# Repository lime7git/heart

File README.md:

# heart
A small gift. Heart shape PCB with STM32L0 microcontroller, TCA6416A I2C GPIO expander, LIS3DH accelerometer, BS812A touch sensor and some fancy leds.
 
It can be used as a keychain. It is operates on a CR2450 coin cell battery. There is a few led patterns which can be start by press a touch button or shake. When the device does not recognize any event in 10 seconds it will enter the low power mode and can be woke up only by touching button. In this mode the power consumption is about 25 uA. 

YouTube video short presentation :

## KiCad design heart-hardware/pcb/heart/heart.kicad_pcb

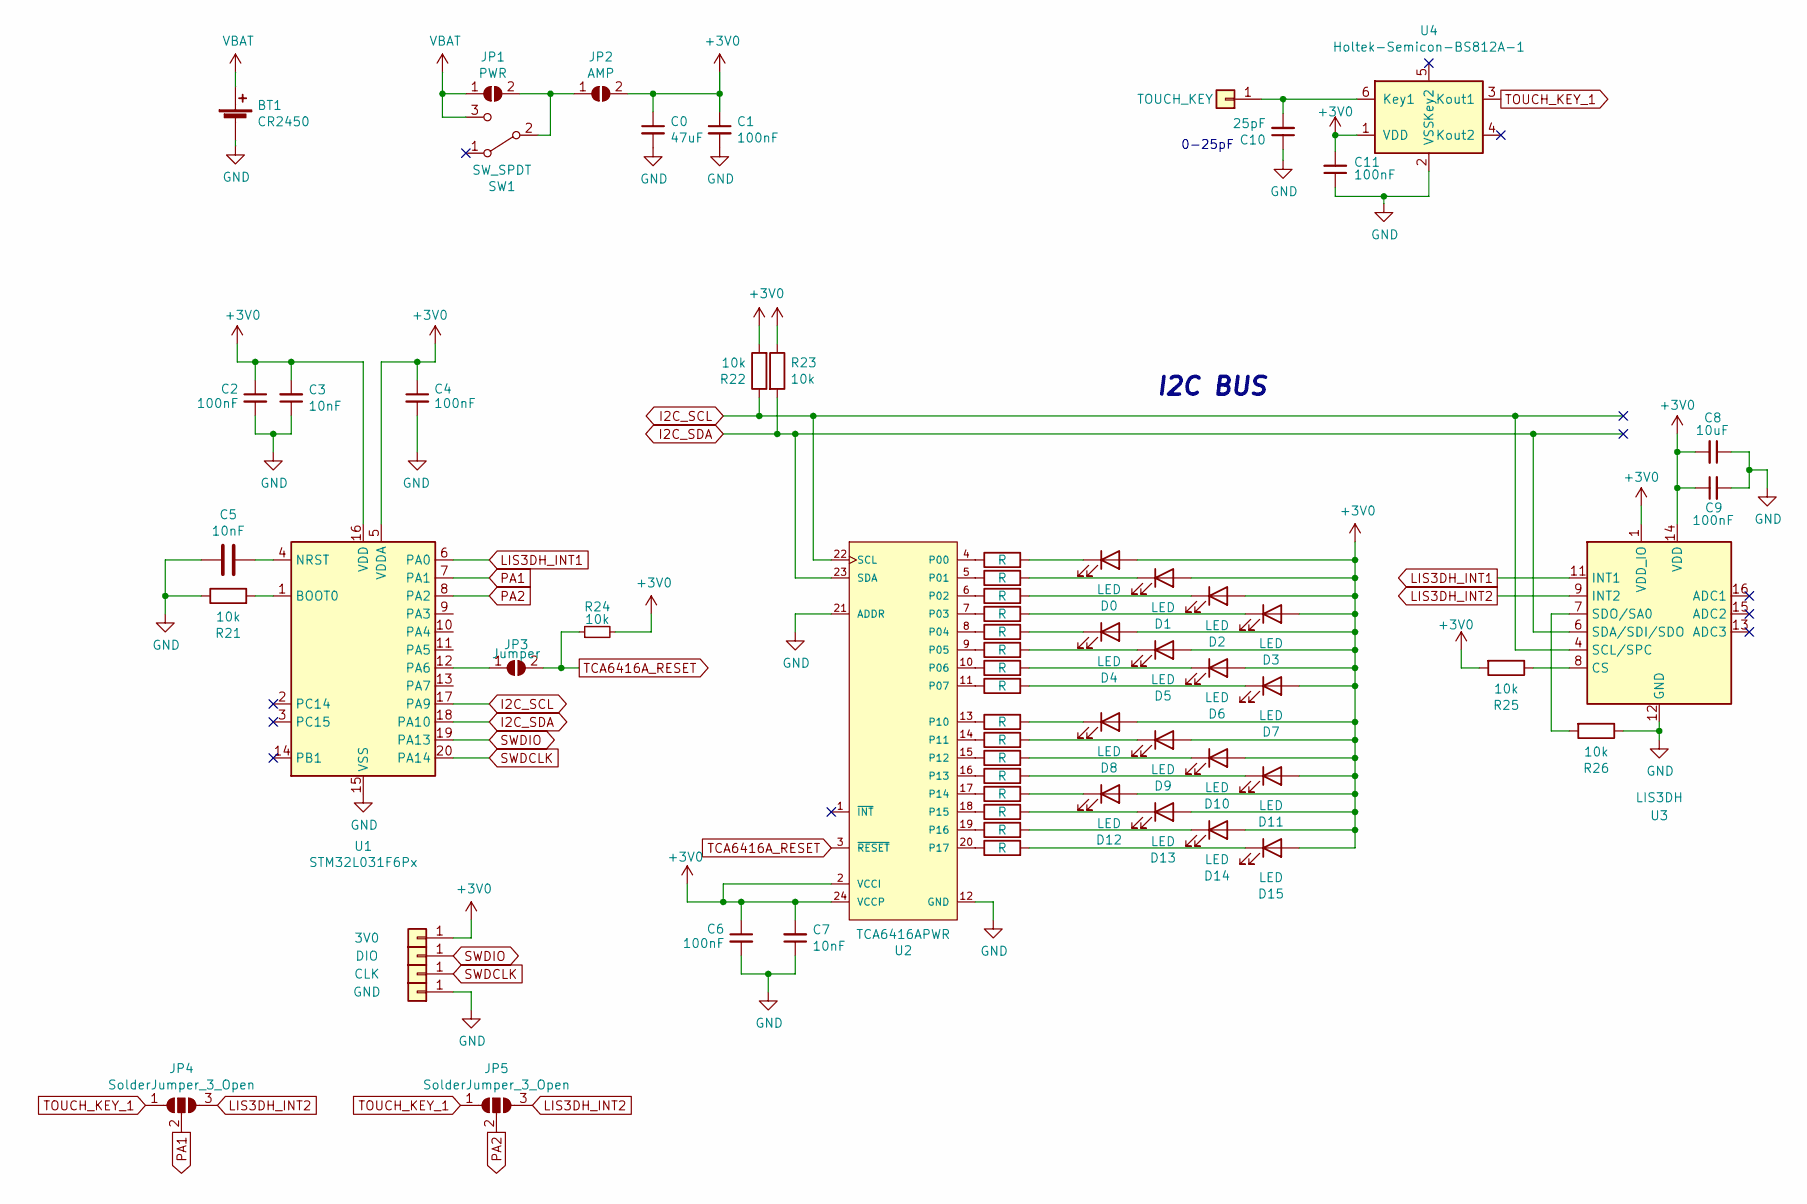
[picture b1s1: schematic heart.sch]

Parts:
BT1: CR2450; BatteryHolder_Keystone_3008_1x2450; LCSC C238100
C0: 47uF; C_1210_3225Metric_Pad1.33x2.70mm_HandSolder; LCSC C2918508
C1: 100nF; C_0402_1005Metric
C2, C4, C6, C9, C11: 100nF; C_0402_1005Metric; LCSC C60474
C3, C5, C7: 10nF; C_0402_1005Metric; LCSC C60133
C8: 10uF; C_0402_1005Metric; LCSC C15525
C10: 25pF; C_0402_1005Metric; LCSC C295971
D0, D1, D2, D3, D4, D5, D6, D7, D8, D9, D10, D11, D12, D13, D14, D15: LED; LED_0603_1608Metric; LCSC C2846646
J1: 3V0; TestPoint_Pad_1.0x1.0mm
J2: DIO; TestPoint_Pad_1.0x1.0mm
J3: CLK; TestPoint_Pad_1.0x1.0mm
J4: GND; TestPoint_Pad_1.0x1.0mm
J5: TOUCH_KEY; TestPoint_Pad_D4.0mm
JP1: PWR; SolderJumper-2_P1.3mm_Open_RoundedPad1.0x1.5mm
JP2: AMP; SolderJumper-2_P1.3mm_Open_RoundedPad1.0x1.5mm
JP3: Jumper; SolderJumper-2_P1.3mm_Open_RoundedPad1.0x1.5mm
JP4, JP5: SolderJumper_3_Open; SolderJumper-3_P1.3mm_Open_RoundedPad1.0x1.5mm_NumberLabels
R0, R1, R2, R3, R4, R5, R6, R7, R8, R9, R10, R11, R12, R13, R14, R15: R; R_0402_1005Metric; LCSC C258126
R21, R22, R23, R24, R25, R26: 10k; R_0402_1005Metric; LCSC C258091
SW1: SW_SPDT; SW_SPDT_PCM12; LCSC C221841
U1: STM32L031F6Px; TSSOP-20_4.4x6.5mm_P0.65mm; LCSC C115208
U2: TCA6416APWR; TSSOP-24_4.4x7.8mm_P0.65mm; 5V Tolerant IO Yes; LCSC C130203
U3: LIS3DH; LGA-16_3x3mm_P0.5mm_LayoutBorder3x5y; LCSC C15134
U4: Holtek-Semicon-BS812A-1; SOT-23-6; LCSC C81747

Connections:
+3V0: C0.1, C1.1, C2.1, C3.2, C4.1, C6.1, C7.2, C8.2, C9.1, C11.2, D0.2 (A), D1.2 (A), D2.2 (A), D3.2 (A), D4.2 (A), D5.2 (A), D6.2 (A), D7.2 (A), D8.2 (A), D9.2 (A), D10.2 (A), D11.2 (A), D12.2 (A), D13.2 (A), D14.2 (A), D15.2 (A), J1.1, JP2.2 (B), R22.2, R23.1, R24.2, R25.2, U1.5 (VDDA), U1.16 (VDD), U2.2 (VCCI), U2.24 (VCCP), U3.1 (VDD_IO), U3.14 (VDD), U4.1 (VDD)
GND: BT1.2 (-), C0.2, C1.2, C2.2, C3.1, C4.2, C5.2, C6.2, C7.1, C8.1, C9.2, C10.1, C11.1, J4.1, R21.1, R26.1, U1.15 (VSS), U2.12 (GND), U2.21 (ADDR), U3.5 (GND), U3.10 (GND), U3.12 (GND), U4.2 (VSS); also elsewhere on the board
I2C_SCL: R22.1, U1.17 (PA9), U2.22 (SCL), U3.4 (SCL/SPC)
I2C_SDA: R23.2, U1.18 (PA10), U2.23 (SDA), U3.6 (SDA/SDI/SDO)
LIS3DH_INT1: U1.6 (PA0), U3.11 (INT1)
LIS3DH_INT2: JP4.3 (B), JP5.3 (B), U3.9 (INT2); also elsewhere on the board
unnamed: C5.1, U1.4 (NRST)
unnamed: C10.2, J5.1, U4.6 (Key1)
unnamed: D0.1 (K), R0.2
unnamed: D1.1 (K), R1.2
unnamed: D2.1 (K), R2.2
unnamed: D3.1 (K), R3.2
unnamed: D4.1 (K), R4.2
unnamed: D5.1 (K), R5.2
unnamed: D6.1 (K), R6.2
unnamed: D7.1 (K), R7.2
unnamed: D8.1 (K), R8.2
unnamed: D9.1 (K), R9.2
unnamed: D10.1 (K), R10.2
unnamed: D11.1 (K), R11.2
unnamed: D12.1 (K), R12.2
unnamed: D13.1 (K), R13.2
unnamed: D14.1 (K), R14.2
unnamed: D15.1 (K), R15.2
unnamed: JP1.2 (B), JP2.1 (A), SW1.2 (B)
unnamed 25: JP3.1 (A), U1.12 (PA6); also elsewhere on the board
unnamed: R0.1, U2.4 (P00)
unnamed: R1.1, U2.5 (P01)
unnamed: R2.1, U2.6 (P02)
unnamed: R3.1, U2.7 (P03)
unnamed: R4.1, U2.8 (P04)
unnamed: R5.1, U2.9 (P05)
unnamed: R6.1, U2.10 (P06)
unnamed: R7.1, U2.11 (P07)
unnamed: R8.1, U2.13 (P10)
unnamed: R9.1, U2.14 (P11)
unnamed: R10.1, U2.15 (P12)
unnamed: R11.1, U2.16 (P13)
unnamed: R12.1, U2.17 (P14)
unnamed: R13.1, U2.18 (P15)
unnamed: R14.1, U2.19 (P16)
unnamed: R15.1, U2.20 (P17)
unnamed: R21.2, U1.1 (BOOT0)
unnamed: R25.1, U3.8 (CS)
unnamed: R26.2, U3.7 (SDO/SA0)
PA1: JP4.2 (C), U1.7 (PA1); also elsewhere on the board
PA2: JP5.2 (C), U1.8 (PA2); also elsewhere on the board
SWDCLK: J3.1, U1.20 (PA14)
SWDIO: J2.1, U1.19 (PA13)
TCA6416A_RESET: JP3.2 (B), R24.1, U2.3 (~RESET~); also elsewhere on the board
TOUCH_KEY_1: JP4.1 (A), JP5.1 (A), U4.3 (Kout1); also elsewhere on the board
VCC: BT1.1 (+), JP1.1 (A), SW1.3 (C); also elsewhere on the board

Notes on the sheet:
I2C BUS
0-25pF

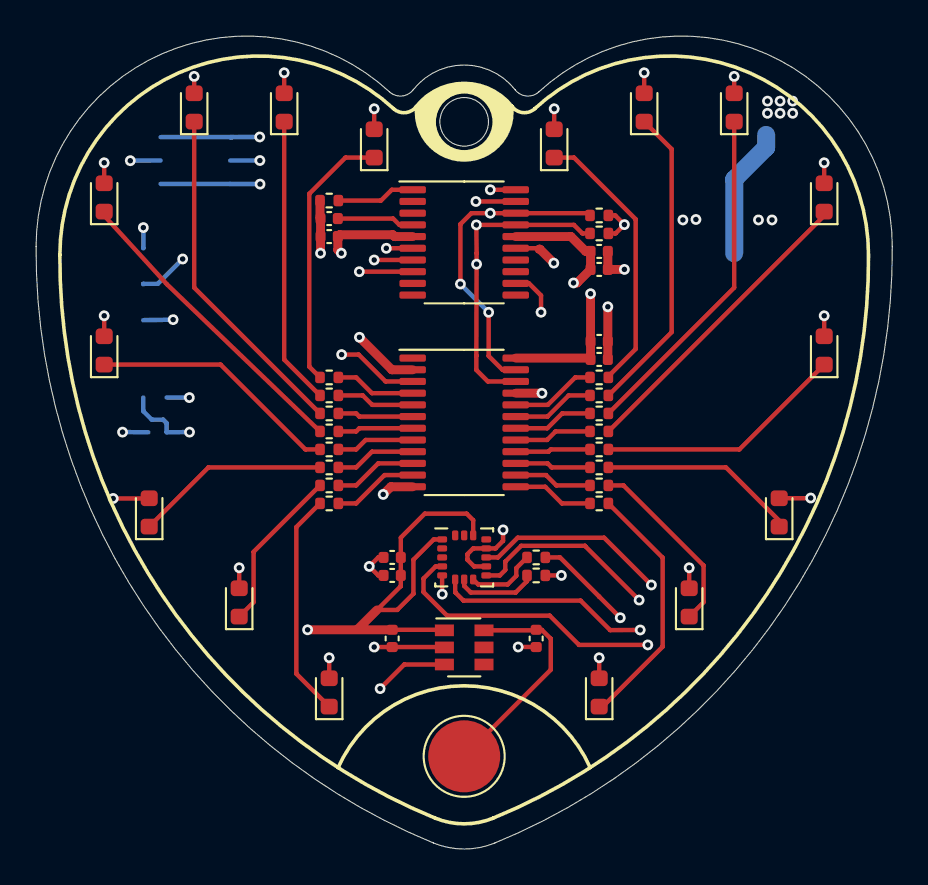
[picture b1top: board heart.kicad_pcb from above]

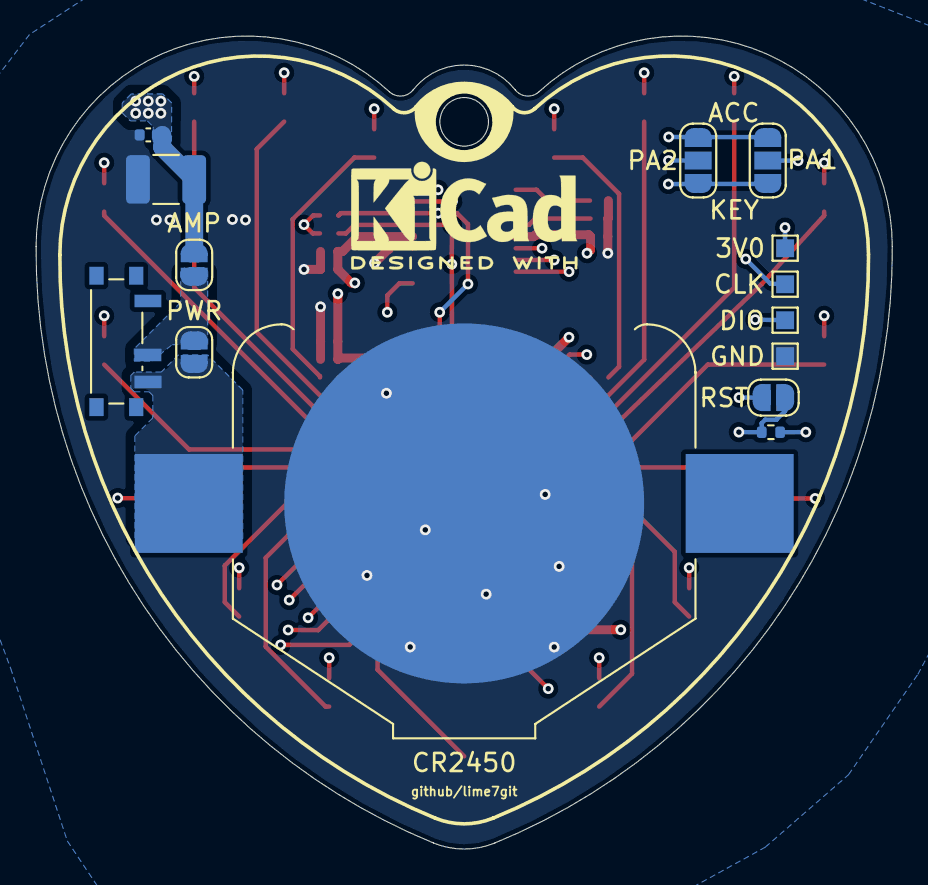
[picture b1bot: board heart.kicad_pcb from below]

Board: 4 copper layers, 47.6 x 45.2 mm, 66 parts (14 on the bottom side), 52 nets.

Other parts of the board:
CR2450: CR2450; BatteryHolder_Keystone_3008_1x2450
PA1, PA2: SolderJumper_3_Open; SolderJumper-3_P1.3mm_Open_RoundedPad1.0x1.5mm_NumberLabels
RST: Jumper; SolderJumper-2_P1.3mm_Open_RoundedPad1.0x1.5mm

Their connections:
GND: CR2450.2; also elsewhere on the board
LIS3DH_INT2: PA1.3, PA2.3; also elsewhere on the board
unnamed 25: RST.1; also elsewhere on the board
PA1: PA1.2; also elsewhere on the board
PA2: PA2.2; also elsewhere on the board
TCA6416A_RESET: RST.2; also elsewhere on the board
TOUCH_KEY_1: PA1.1, PA2.1; also elsewhere on the board
VCC: CR2450.1; also elsewhere on the board

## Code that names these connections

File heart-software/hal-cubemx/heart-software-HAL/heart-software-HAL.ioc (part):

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Mcu.Name=STM32L031F(4-6)Px
Mcu.Package=TSSOP20
Mcu.UserName=STM32L031F6Px
PA0-CK_IN.GPIOParameters=GPIO_Label
PA0-CK_IN.GPIO_Label=LIS3DH_INT1
PA0-CK_IN.Signal=GPIO_Input
PA1.GPIOParameters=GPIO_Label
PA1.GPIO_Label=LIS3DH_INT2
PA1.Signal=GPIO_Input
PA10.GPIOParameters=GPIO_Pu
PA10.GPIO_Pu=GPIO_PULLUP
PA10.Mode=I2C
PA10.Signal=I2C1_SDA
PA13.Mode=Serial_Wire
PA13.Signal=SYS_SWDIO
PA14.Mode=Serial_Wire
PA14.Signal=SYS_SWCLK
PA2.GPIOParameters=GPIO_Label,GPIO_ModeDefaultEXTI
PA2.GPIO_Label=TOUCH_BUTTON
PA2.GPIO_ModeDefaultEXTI=GPIO_MODE_IT_RISING_FALLING
PA2.Signal=GPXTI2
PA6.GPIOParameters=GPIO_Label
PA6.GPIO_Label=TCA6416A_RESET
PA6.Signal=GPIO_Output
PA9.GPIOParameters=GPIO_Pu
PA9.GPIO_Pu=GPIO_PULLUP
PA9.Mode=I2C
PA9.Signal=I2C1_SCL
RCC.HSE_VALUE=8000000
RCC.SYSCLKFreq_VALUE=262144
board=custom

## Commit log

2021-12-21 PCB Design
    Left probably only add some decoupling capacitors.
2021-12-21 Added some datasheets
2021-12-21 Deleted unused libraries
2021-12-21 Added current probe test points
2021-12-22 Added decoupling capacitors
2021-12-23 Schematic complete (ver. 1.0), starting work on a pcb and choose footprints
2021-12-23 Added vector graphics of heart shape, used as a pcb edges
2021-12-24 PCB design update
2021-12-24 Bottom layer component set
2021-12-26 Added touch key
2021-12-27 Changed battery from 2x CR2032 to 1x CR2450
2021-12-27 New final heart shape
2021-12-27 New heart shape, battery change, top layer component placed v1
2021-12-27 All components initially placed
2021-12-27 Component pacement v1
2021-12-27 Start routing traces
2021-12-27 Added jumper to choose interuppt lines
2021-12-27 Routing in progress
2021-12-28 Some trace routed, backup with vias on leds to trace route in inner layer
2021-12-28 Gerber files for test
2021-12-28 Route completed
2021-12-28 Added documentation for touch sensor ic
2021-12-28 Added addnotation to github's profile
2021-12-28 Version 1.0
2021-12-28 Production files gerber ver. 1.01
2021-12-28 Version 1.01, change power planes clearance
2021-12-29 Gerber files ver 1.02
2021-12-29 Version 1.02
2022-01-01 Generate drill map for produce
2022-01-30 Software test using CubeMX and HAL library
2022-01-30 Create ibom.html, an interactive HTML bom project from 'openscopeproject'
    Using https://github.com/openscopeproject/InteractiveHtmlBom
2022-01-30 Software test update
2022-01-31 Test software update
    3 sequences starting with a touch button
2022-01-31 Added new sequention
2022-01-31 Sequence update
2022-02-08 Test software update
2022-02-08 Trying to get 3d model file from kicad to make a solidwork's render
2022-02-13 Added some photos and videos
2022-02-13 Software update
2022-02-16 hal cube mx update
2022-02-16 Visual studio stm32cube framework test software
2022-02-16 Visual studio cmsis framework software main
2022-02-16 clock and i2c configuration
2022-02-16 I2C not tested yet
2022-02-16 dummy
2022-02-16 Working on i2c bus
2022-02-16 Added build flag so that libraries can see includes
2022-02-21 Update comments and documentation
2022-02-21 Change MSI clock frequency test
2022-02-21 Fix after computer format
2022-02-21 Documentation update
2022-02-21 Clock setup
2022-03-02 HAL software rework
2022-03-02 cmsis i2c communication problems
2022-03-03 Sequencies
2022-03-03 First ten test sequencies
2022-03-05 RTC pseudo random sequency
2022-03-13 touch button input capture random sequencies
2022-03-13 Added some documentatnions
2022-03-17 RTC time/date setup
2022-06-22 accelerometer lis3dh data polling
2022-06-22 accelerometer; shake detection, double click detection
2022-10-06 update, delete of unused and better random generator
2022-10-06 first iteration of pvd low battery voltage detection
2022-10-06 low battery detection
2022-10-09 rtc wakeup, better low power modes
2022-10-09 dwa tryby uruchamiania, touch button mode i acc mode
2022-10-09 added reset cause
2022-10-09 version 1
2022-12-18 lptim implementation
2023-01-01 version 2.0
    new state machine, sleep mode after 10 sec idle, one operational mode
2023-01-01 100Hz accelerometer data output
2023-01-06 sprawdzanie stanu flagi pvdo w kazdej petli low battery state
2023-01-25 better pvd recognition
